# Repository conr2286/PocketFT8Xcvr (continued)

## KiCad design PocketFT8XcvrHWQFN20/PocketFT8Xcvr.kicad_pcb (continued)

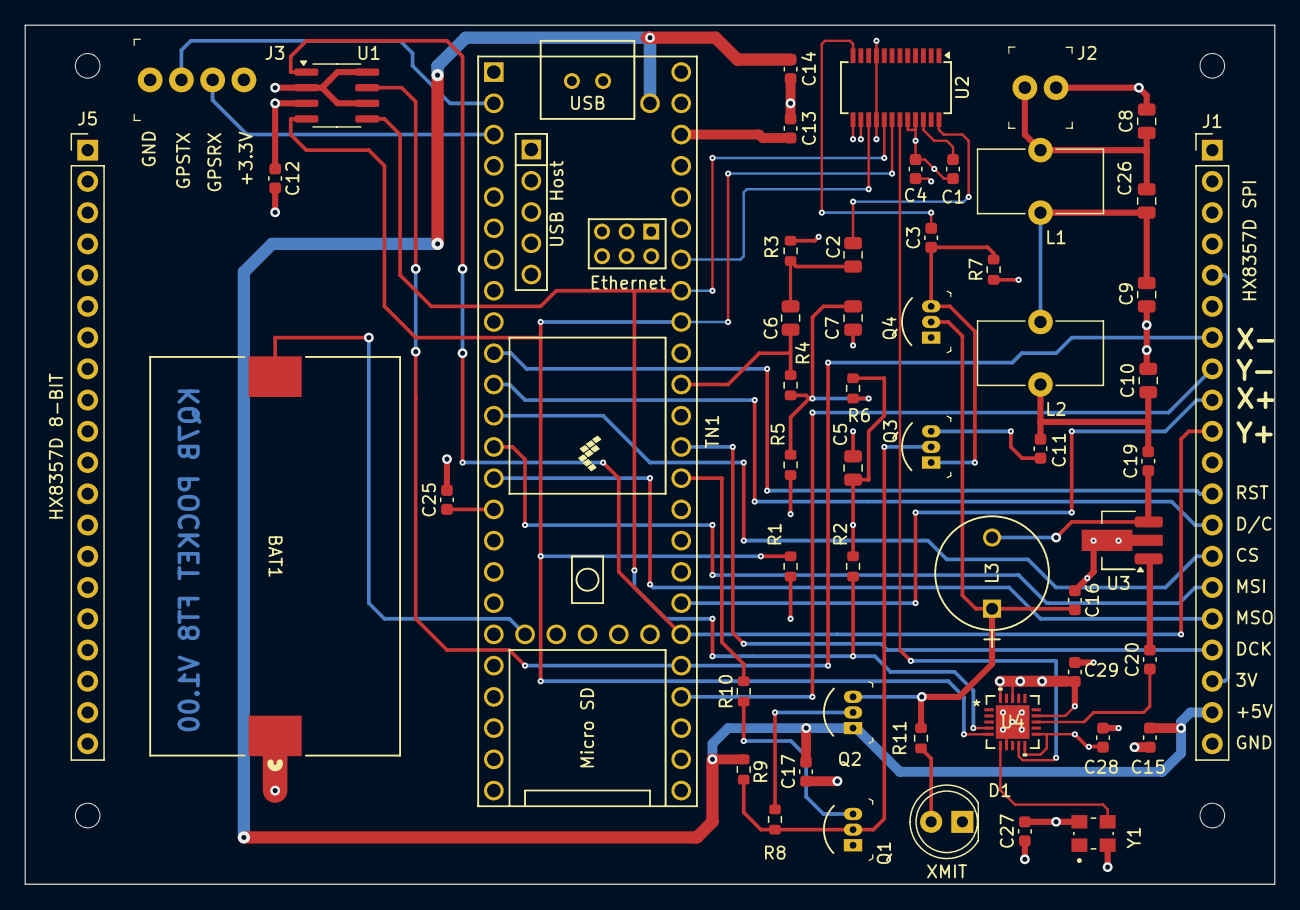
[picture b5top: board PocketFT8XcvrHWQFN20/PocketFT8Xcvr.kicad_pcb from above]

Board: 4 copper layers, 101.6 x 69.9 mm, 54 parts (0 on the bottom side), 42 nets.

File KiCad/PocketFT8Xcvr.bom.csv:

Reference,Value,Footprint,Qty,#,Manufacturer,Description,Notes,Mfg Part #,Type
Y1,ASTX-H11-25.000MHZ-T,ASTX_H11_25_000MHZ_T:XTAL_ASTX-H11-25.000MHZ-T,1,1,Abracon,ASTX-H11-25.000MHZ-T.  -30 ~ +75C,,ASTX-H11-25.000MHZ-T,SMD
U3,GVA-84+,Package_TO_SOT_SMD:SOT-89-3_Handsoldering,1,2,Mini-Circuits,"DC-7000MHz +16dB Gain Block, SOT-89",hand soldering footprint used for better heat sink,GVA-84+,SMD
U2,Si4735-D60-GU,Package_SO:SSOP-24_3.9x8.7mm_P0.635mm,1,3,Skyworks Solutions,RF RX AM/FM 153KHZ-279KHZ 24SSOP,,SI4735-D60-GU,SMD
U1,MCP3422A1T-E/SN,Package_SO:SOIC-8_3.9x4.9mm_P1.27mm,1,4,Microchip Technology,IC ADC 18BIT SIGMA-DELTA 8SOIC,,MCP3422A1T-E/SN,SMD
"R9,R10",5.1K,Resistor_SMD:R_0603_1608Metric,2,5,Yageo,RES 5.1K OHM 5% 1/10W 0603,Substitutions OK,RC0603JR-075K1L,SMD
"R8,R11",510 Ohm,Resistor_SMD:R_0603_1608Metric,2,6,Yageo,RES 510 OHM 5% 1/10W 0603,Substitutions OK,RC0603JR-07510RL,SMD
R7,51 OHM,Resistor_SMD:R_0603_1608Metric,1,7,Yageo,RES 51 OHM 5% 1/2W 1210,Substitutions OK,RC1210JR-0751RL,SMD
R6,10K,Resistor_SMD:R_0603_1608Metric,1,8,Yageo,RES 47.0K OHM 1/8W 0805 SMD,Substitutions OK,RC0603JR-0710KL,SMD
"R3,R4",47K,Resistor_SMD:R_0603_1608Metric,2,9,Yageo,RES 47K OHM 1/10W 5% 0603,Substitutions OK,RC0603JR-0747KL,SMD
"R1,R2,R5",2.0K,Resistor_SMD:R_0603_1608Metric,3,10,Yageo,RES 2K OHM 5% 1/10W 0603,Substitutions OK,RC0603JR-072KL,SMD
IC1,SI5351C-B-GM1,SI5351C-B-GM1:QFN50P300X300X90-17N-D,1,11,Skyworks,"Clock Generators & Support Products I2C programmable, any-frequency, any-output, reference clock input, 4-output LVCMOS clock generator",,,
"C2,C5,C6,C7",10UF,Capacitor_SMD:C_0805_2012Metric,4,12,Kemet,CAP CER 10UF 16V X5R 0805,Substitutions OK,C0805C106K4PAC7800,SMD
"C1,C3,C4,C11,C12,C13,C14,C15,C16,C17,C19,C20,C25,C27,C28,C29",0.1UF,Capacitor_SMD:C_0603_1608Metric,16,13,Kemet,CAP CER 0.1UF 16V X7R 0603,Substitutions OK,C0603C104K4RAC7867,SMD
BAT1,BU2032SM-JJ-GTR,BU2032SM-JJ-GTR_MPD,1,14,MPD (Memory Protection Devices),BATT HOLDER COIN 20MM 1 CELL SMD,Must mount topside,BU2032SM-JJ-GTR,SMD

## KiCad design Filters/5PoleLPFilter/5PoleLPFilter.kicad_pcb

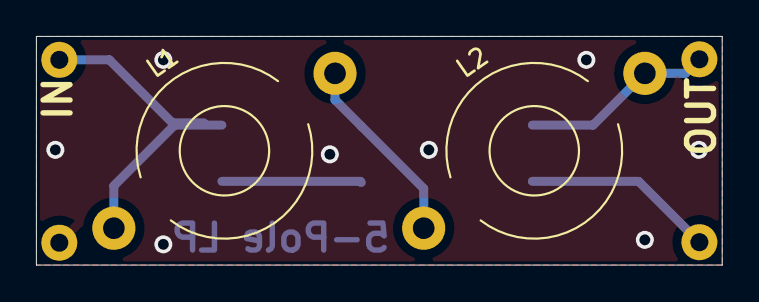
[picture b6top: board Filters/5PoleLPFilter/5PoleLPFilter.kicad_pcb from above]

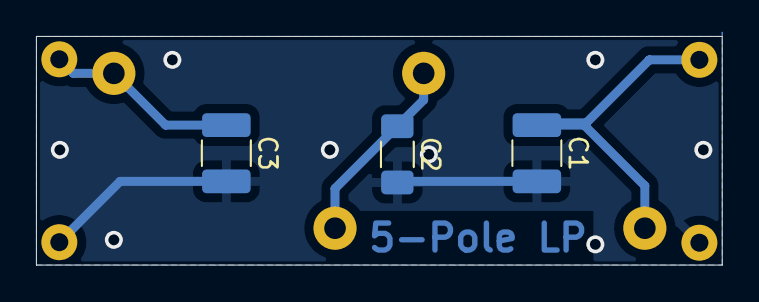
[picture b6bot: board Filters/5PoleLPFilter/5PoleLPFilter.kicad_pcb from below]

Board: 2 copper layers, 38.1 x 12.7 mm, 6 parts (3 on the bottom side), 4 nets.

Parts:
C1, C3: 1000pF; C_1210_3225Metric_Pad1.33x2.70mm_HandSolder
C2: 1300pf; C_1206_3216Metric_Pad1.33x1.80mm_HandSolder
J1: FilterConn02
L1, L2: 1.2uH; L_Toroid_Horizontal_D9.5mm_P15.00mm_Diameter10-5mm_Amidon-T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

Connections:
GND: C1.2, C2.2, C3.2, J1.2
unnamed: C1.1, L1.1
unnamed: C2.1, L1.2, L2.1
unnamed: C3.1, L2.2

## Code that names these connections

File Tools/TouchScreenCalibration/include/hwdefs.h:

#pragma once
/*
**
** NAME
**  pins.h --- Define usage of all GPIO pins in this one place
**
** NOTES
**  If you change processors, displays, etc, you may need to reevaluate the GPIO pin assignments
**
**  Many of the PIN_* names reflect their labels in the schematic
**
**  The V2.0 boards control the RCV and XMT signals using firmware thru PIN_RCV and PIN_XMT.
**  This firmware implementation is compatible with both V1.X and V2.0 boards.
**
**  V2.X and V3.X boards use an MCP342X external 12-bit ADC to read the touchscreen signals.
**
**  V4.X boards eliminate the MCP342X and read the touchscreen through ADC1 A16 and A17 while
**  the Teensy 4.1 audio pipeline uses ADC2 and A2.
**
** HISTORY
**  10/08/2024 Teensy 4.1 pin assignments by KQ7B
**  03/14/2026 Version 4.X boards move the touchscreen to Teensy 4.1's A16 and A17 pins
**
**/

// Define the hardware version number (whole integral values only)
// #define HW_VERSION 2        //Version 2.X boards (working lab prototype)
// #define HW_VERSION 3        // Version 3.X boards (never mfg'd due to tariffs)
#define HW_VERSION 4  // Version 4.X boards (uses internal touchscreen ADC)

// The Adafruit 480x320 display pins
#define PIN_CS 10
#define PIN_DC 9
#define PIN_DRST 8
#define PIN_MOSI 11
#define PIN_DCLK 13  // Teensy 4.1
#define PIN_MISO 12

// I2C pins
#define PIN_SCL 19   // Wire
#define PIN_SDA 18   // Wire
#define PIN_SCL2 24  // Wire2
#define PIN_SDA2 25  // Wire2

// I2C bus definitions for the Wire objects
#define WIRE_RCV Wire   // The SI4735's private bus
#define WIRE_ETC Wire2  // Everything (SI5351, MCP342x) else

// Serial bus definitions for optional GPS
#define SerialGPS Serial1

// SI4735 pins
#define PIN_RRST 20  // Resets the Si4735
#define PIN_AF A2    // Si4735 received audio connected to A2 via Pin 16

// Transmit/Receive pins
#define PIN_XMT 14  // Teensy 4.1
#define PIN_RCV 15  // FW implementation of ~PTT (i.e. RECV) in V2.0 boards

// Adafruit resistive touchscreen pins (External ADC HW option)
#define PIN_YR 38  //
#define PIN_XR 37  //
#define PIN_YM 36  // Any digital pin
#define PIN_XP 39  // Any digital pin

#if HW_VERSION >= 4
// Version 4.X hardware internal Teensy 4.1 ADC pins (Note:  Versions 2.X and 3.x
// use an external ADC read via I2C rather than an internal ADC) for reading the
// touchscreen pins (Schematic signals XDM and YDP).  Note:  You can
// patch a V3.X PCB to make these signal connections for the internal ADC
#define PIN_XM A16  // Y-Coord analog input signal sampled from display's floating XM pin (A16)
#define PIN_YP A17  // X-Coord analog input signal sampled from display's floating YP pin (A17)
#endif

// GPS pins (Teensy 4.1 Serial1)
#define PIN_GPSTX 0  // TX data from GPS
#define PIN_GPSRX 1  // RX data from GPS
#define PIN_PPS 2    // PPS pulse

// Auxilliary pins for future expansion (Require V3+ PCB)
#define PIN_AN13 27  // A13
#define PIN_D27 27   // D27
#define PIN_D28 28   // D28
#define PIN_D29 29   // D29
#define PIN_D30 30   // D30
#define PIN_D31 31   // D31

// The ADC calibration data for V4.X hardware is using a 3.3V reference to Vcc
// And analog.c is using a 10-bit resolution rather than the MCP342X 12-bits.
#if HW_VERSION >= 4
#define TS_MINX (137 >> 2)
#define TS_MINY (126 >> 2)
#define TS_MAXX (2182 >> 2)
#define TS_MAXY (1392 >> 2)
#define MINPRESSURE (120 >> 2)  // I don't think the pressure stuff is working as expected
#define PENRADIUS 3
#else
// This is calibration data for the MC342x ADC to the screen coordinates
// using 510 Ohm resistors to reduce the sensors' driven voltage to Y+ and X-
// where the ADC reference voltage is 2.048 volts, and sampling at 12-bits.
#define TS_MINX 123
#define TS_MINY 104
#define TS_MAXX 1715
#define TS_MAXY 1130
#define MINPRESSURE 120  // I don't think the pressure stuff is working as expected
#define PENRADIUS 3
#endif

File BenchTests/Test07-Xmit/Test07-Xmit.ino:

/**
NAME
  Test07-Si5351 -- Test the entire transmitter's RF chain

DESCRIPTION
  Initializes the Si5351 and programs CLK0 and CLK2.  If successful,
  CLK0 (XCLK, the transmitter clock) will output a 14100 kHz signal.
  Both signals should be confirmed with a frequency counter at the
  antenna connector.

EXERCISED,
  + I2C bus
  + Si5351 connectivity
  + TCXO and Si5351 operation
  + PTT and transmitter's RF chain
  + V2.00 hardware implements the complementary XMIT and RECV signals in firmware
  + V2.00 hardware moved the SI5351 from the Wire to Wire1 bus

NOTE
  + This is the first use of the TCXO whose 25.000 mHz signal
  appears on its pin 3 and on the Si5351 CLKIN pin 6
  + The CLK0 XCLK signal appears on Si5351 pin 13, C20 and U3 pin 1
  + The CLK2 RCLK signal appears on Si5351 pin 9 and Si4735 pin 19

REFERENCES


ATTRIBUTION
  KQ7B 

**/

#include "si5351.h"
#include <Wire.h>

// Set I2C bus to use: Wire, Wire1, etc.
#define WIRE Wire2

//Exercise the Push-to-Talk Pin
#define PIN_PTT 14
#define PIN_RCV 15

Si5351 si5351;

void setup() {
  bool err;

  Serial.begin(9600);
  delay(100);
  printf("Starting...\n");

  //Initialize SI5351 (load cap won't actually be used with CLKIN) for Pocket FT8
  bool found = si5351.init(SI5351_CRYSTAL_LOAD_8PF, 25000000, 0L);
  if (!found) {
    printf("Error:  SI5351 not found\n");
    while (1)
      ;  //Hang here
  }

  //Configure SI5351 PLLs to use external CLKIN rather than XTAL
  si5351.set_pll_input(SI5351_PLLA, SI5351_PLL_INPUT_CLKIN);  //KQ7B V1.00 uses cmos CLKIN, not a XTAL
  si5351.set_pll_input(SI5351_PLLB, SI5351_PLL_INPUT_CLKIN);  //All PLLs using CLKIN
  si5351.set_pll(SI5351_PLL_FIXED, SI5351_PLLA);
  si5351.set_freq(3276800ULL, SI5351_CLK2);  //Receiver's PLL clock (so sad)
  si5351.output_enable(SI5351_CLK2, 1);      //Enable receiver clk (TP3 on PCB)

  //Configure xmit CLK0 for 14.1 mHz
  err = si5351.set_freq(1410000000ULL, SI5351_CLK0);
  if (err) {
    printf("Error:  set_freq(...,CLK0\n");
    while (1)
      ;
  }
  si5351.output_enable(SI5351_CLK0, 1);  //Enable transmitter clk (TP2 on PCB)


  //Turn on the transmitter's RF chain
  pinMode(PIN_RCV, OUTPUT);
  pinMode(PIN_PTT, OUTPUT);
  digitalWrite(PIN_RCV, LOW);   //~RCV
  digitalWrite(PIN_PTT, HIGH);  //XMT
}


void loop() {

  //Output SI5351 status every 10 seconds
  si5351.update_status();
  Serial.print("SYS_INIT: ");
  Serial.print(si5351.dev_status.SYS_INIT);
  Serial.print("  LOL_A: ");
  Serial.print(si5351.dev_status.LOL_A);
  Serial.print("  LOL_B: ");
  Serial.print(si5351.dev_status.LOL_B);
  Serial.print("  LOS: ");
  Serial.print(si5351.dev_status.LOS);
  Serial.print("  REVID: ");
  Serial.println(si5351.dev_status.REVID);

  delay(10000);
}

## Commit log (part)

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2024-10-26 Ongoing filter daughter board development
2024-10-28 Both the main board and filter board submitted to PCBway
2024-11-07 Document xmit/recv switching better
2024-11-07 Better documentation of xmit/recv switching
2024-11-11 40 Meter Bandpass Filter LTspice Simulation
    LTspice was used to evaluate the performance of the 40M bandpass filter
2024-11-22 Preparing bench tests and investigations for V2.00 hardware
    V2.00 hardware has a second I2C bus, a new SN74ACT244 PA, serial support for a GPS, and the complimentary XMT/RCV signals are now implemented in firmware to avoid an unnecessary gate.
2024-11-27 Ongoing prep for V2.00 hardware
2024-11-27 future ideas
2024-12-02 Investigating I2C failure on V2.00 HW
2024-12-03 Resolve Issue #24. Test04-I2C didn't find the SI4735 on SDA/SCL
2024-12-04 Fixing tests for V2.00 boards
2024-12-05 Debugging SI5351 test
    Output frequency off by 100X??? Does set_freq() really want 1/100 Hz resolution? Or has something went wrong?
2024-12-06 Ongoing turn-on of V2.00 boards
2024-12-08 Cleaning up I2C bus definitions
2024-12-08 Tinkering with pins to exercise V1.10 hardware
2024-12-08 tinkering with old recvr code
2024-12-09 Working on gps time
2024-12-09 Issue #23: Isolating SI4735 on a private I2C bus resolves noise/reception issue
    The V2.00 hardware places SI4735 on Wire, and the SI5351 and MCP342x on Wire2 busses.
2024-12-09 Switching to revised version of Test05-Touchpad
2024-12-10 Filter investigations
2024-12-11 Ongoing work to get GPS derived date, time and location working
2024-12-11 Ongoing work on GPS
2024-12-12 Cleaning up some of the dangerous string copies
2024-12-12 Ongoing cleanup of dangerous string operations
2024-12-13 Ongoing prep for logging ADIF
2024-12-13 Ongoing prep work for logging
2024-12-18 Ongoing implementation of logging
2024-12-21 Gathered all the filter designs/models into one folder
2024-12-29 In progress: Instrumenting code to learn about FT8 decoding and howto log a qso
2024-12-29 Ongoing investigation of decoded messages and how CQ is handled
2024-12-31 New bandpass filter PCB and ft8 decoding investigation
2025-01-04 Ongoing investigation of ft8 decoding
2025-01-06 Installing debugging code for transmitted FSK #38
2025-01-11 #39 Transmit timing greatly improved
    Now running a couple hundred milliseconds late.
2025-01-12 Minor GUI improvements
2025-01-21 Mitigate time spent in fillRect() erasing displayed messages
2025-01-22 Misc performance improvements around displaying received messages
    fillRect() is amazingly slow! :(
2025-01-27 Ongoing development of Sequencer
    unpack:202 is recognizing RR73 as a locator
2025-02-02 Sequencer can call CQ and sustain QSO with 2nd KQ7B operator
2025-02-03 Sequencer bug fixes
2025-02-03 Code now builds with Visual Studio Code and PlatformIO
2025-02-03 Testing VSC source control
2025-02-04 Debugging Sequencer in progress
2025-02-04 Moved logging code in .../lib folder
2025-02-07 GPS PPS
2025-02-07 Add PPS signal to hardware
2025-02-07 Info message enhancements
2025-02-07 Sequencer messaging tweeks
2025-02-11 Pocket FT8 Revisited made a QSO with a real remote station
2025-02-12 ADIF logging is now working
2025-02-12 Reorganizing
2025-02-12 Ongoing reorganization of custom library code
2025-02-12 Updating documentation for PlatformIO and V2.00
2025-02-19 Update Sequencer.cpp
    timeslotEvent() was missing a case for LISTEN_RRR
2025-02-19 Fix #54 and #55
    ADIF log now reports transmitter power and rig name.
    Sequencer now distinguishes "CQ" from "CQ DX" and related targeted CQs
2025-02-20 Housekeeping for upcoming release
2025-02-20 Enable RoboOp to automatically respond to CQ messages
2025-02-22 Work on #56 in progress
2025-02-25 Misc cleanup and memory savings
2025-03-02 Ongoing evolution of a host datalink
2025-03-17 Moved CommLink Folder to Investigations
    Pivot to a mechanical solution for extracting ADIF log file
2025-03-18 Cleanup after removing CommLink
2025-03-20 #57 GUI now indicates RECEIVE/PENDING/TRANSMIT/TUNING
2025-03-21 Cleanup
2025-03-23 Now using FT8Font replacing 5X7 font
2025-03-28 A_GUI implementation in progress in Investigations
    + Bug fixes for HX835_t3n which fails to include SP char in getTextBounds() calculation. FIx: Treat ' ' like a '_' char.
2025-03-29 Investigating use of an ADisplay virtual base class
2025-03-30 Cleanup of AGUI before implementing more widgets
2025-04-06 AGUI progress
2025-04-06 AListBox working code cleanup
2025-04-08 AGUI reorganization of app defaults
2025-04-08 Ongoing AGUI
2025-04-09 AGUI AListBox and AButton now pass simple tests
2025-04-10 cleanup stash
2025-04-11 AGUI ongoing develppment
2025-04-11 Rename AGUI investigation folder
2025-04-11 Brought lib AGUI into PocketFT8XcvrFW
2025-04-12 Several AGUI widgets passing user interface tests
2025-04-13 AGUI cleanup
2025-04-15 Ongoing implementation of AGUI in Pocket FT8 Revisited
2025-04-16 Ongoing AGUI test/feature development
2025-04-16 Connect XCLK to MCU
    We may use the GPS PPS timing signal to instrument the accuracy of XCLK operating at, say, 1 mHz and thus derive a calibration adjustment for the TCXO.
2025-04-18 AGUI Tests passing
2025-04-19 Implemented StationInfo in AGUI
2025-04-20 Ongoing AGUI integration
2025-04-20 Ongoing integration of AGUI
2025-04-22 Rewrote AListBox which now passes tests
2025-04-23 Implemented timeout for ancient Station Messages
2025-04-23 Updated LOGFILE.ADIF example
2025-04-23 Move some code to FLASHMEM
2025-04-23 Updated documentation
2025-04-25 Misc UI
2025-04-27 Adding UI support for touching Station Messages
2025-04-27 Enhancements and bugfixes related to new GUI
2025-04-27 Copilot review of AListBox
2025-04-27 Version 2.10
2025-04-29 Refactoring externs
2025-04-30 Refactoring
2025-04-30 Bug fixing
2025-05-01 20M 5-Pole Chebyshev LP Filter
2025-05-02 test_snprintf
2025-05-13 Implement Decode() constructor
2025-05-18 refactor and bug fix
2025-05-20 Reviewing and refactoring
2025-06-06 Update doc
2025-06-06 investigating drawpixel issue in waterfall
2025-07-13 Reordered GPS pins to align with Adafruit Ultimate GPS PA1616S
2025-07-17 Cleanup PCB in progress
2025-07-18 PCB Cleanup
    + GPS signal pins now align with Adafruit's Ultimate GPS to simplify cable
    + Added PPS pin to GPS signals
    + Added extra connector for Teensy analog/digital expansion pins
2025-07-18 PCB V3.00 Cleanup
2025-07-18 Update doc for V3.00 hardware
2025-08-21 V3.00 hardware
2025-09-01 Free Text Messages implemented for buttons M0, M1 and M2 using text from CONFIG.JSON
2025-09-01 Remove DEBUG msgs
2025-09-01 Build on main (new load map)
2025-09-04 Updated doc and exploring Teensy RTC in more detail
2025-09-15 Document MINIMUM_FREQUENCY and MAXIMUM_FREQUENCY
2025-09-15 Create 20Meters.tar.gz
    20Meters.tar.gz contains *eveything* (including hidden .pio files) for a 20 Meter build in .../PocketFT8XcvrFW/.pio/build/teensy41/firmware.hex
2025-09-16 Ignore the load map and comment-out WireIMXRT.h from MCP342x.cpp
2025-09-16 Ignore map
2025-09-17 Ignoring *.map in the future
2025-09-17 Use Charley's PocketFT8XcvrFW with his amplifier stage in audio pipeline
2025-09-17 Place DEFAULT, MINIMUM & MAXIMUM_FREQUENCY in config.h
2025-09-18 Operating frequency now determined entirely by CONFIG.JSON "frequency" entry
2025-09-18 Make hex/firmware.hex available
2025-09-18 Improving RoboOp documentation
2025-09-19 Update commentary in timeslotEvent()
2025-09-19 More documentation of Sequencer.cpp
2025-09-19 Charley's BFO_Offset fix
2025-09-21 Cleanup AGUI documentation (Issue #79)
2025-09-23 Add configurable tcxoCorrection
    Specified in CONFIG.JSON in Hz units
2025-09-24 Removed Changes Made in previous commit.
    Removed Changes Made in previous commit.
    This code agrees with the version on my machine.
2025-10-01 Minor tweaks/doc
2025-10-01 Reorganized tests and added test_touch
2025-10-06 mysteries
2025-10-15 Ready to begin testing callsign hashing
2025-10-16 All unity tests build and pass
2025-10-18 Using new ft8_lib message.cpp, receiver now decodes both standard and nonstandard FT8 message types
2025-10-23 The investigation completed a QSO using a hashed callsign config'd in the Pocket FT8
2025-10-24 Implement unity tests for ft8LibIfce
2025-10-25 Cleaning up crashes arising from new ft8_lib code
2025-10-25 Cleanup DPRINTF, etc
2025-10-25 Refining debug messages
2025-10-25 Ongoing debug refinements
2025-10-26 User real constants in ft8
2025-10-26 Cleanup commentary
2025-11-08 TinySet now passing test_set
2025-12-16 test_agui_covered_widget under development
2025-12-25 AGUI covered widget test in progress
2026-01-21 AGUI now repaints remaining widgets when a widget is deleted
2026-01-22 Ongoing path to separate listening UI from QSO UI
2026-01-25 Debugging new UI
2026-01-25 Moving Station Msg color decisions to UI rather than Sequencer
2026-01-28 Moving UI color and display decisions into UserInterface
2026-01-29 Cleanup following UI changes
2026-01-30 Ongoing refinements/fixes to ui
2026-01-30 Ongoing UI cleanup
2026-01-31 Refactoring UserInterface and Sequencer as Meyers singletons
2026-01-31 Refactor GPShelper as a singleton and eliminate the extern references to its object
2026-01-31 Fixed Sequencer failed to abort CQ
2026-02-02 Refactored AGUI as a Meyers Singleton
2026-02-02 Moved touchscreen calibration parameter into hwdefs.h
2026-02-02 Refactor aspects of waterfall into UserInterface
2026-02-02 Cleanup deprecated code
2026-02-03 Refactor Station as a singleton to clean-up the externs
2026-02-08 Ongoing refactoring and cleanup
2026-02-08 Remove Roger from head of my RSL
2026-02-13 Fixing KiCAD symbols/footprints
    ...damaged by KiCAD upgrade library reorg.
2026-03-08 Minor PCB changes for JLCpcb
2026-03-14 V4 PCB Layout
    Replace MCP342X with Teensy 4.1 internal ADC1 pins A16 and A17
2026-03-14 Minor code cleanups for V4.X
2026-03-14 Submit V4.0 for PCBWay price quote
2026-03-15 Cleanup signal names in firmware to align with schematic
2026-03-15 Disable debugging messages
2026-03-17 V4.01 corrects mistakes in BOM
    Component reduction introduced several errors.
2026-03-19 Cleanup unity tests
2026-03-19 Begin development of hw turn-on test for new boards
2026-03-20 ongoing implementation of test_hw for new boards
2026-03-23 Ongoing hw test development for V4 boards
2026-03-24 Fix missing RCLK signal in test_si4735
2026-03-25 Update 5PoleLP Filter
    + V4.00 Hardware LP Filter PCB
    + Remove deprecated files
2026-03-25 Test cleanup
2026-03-25 Ongoing test development
2026-03-26 touchscreen test investigation
2026-04-14 Ongoing touchscreen improvements
2026-04-14 Ongoing touchscreen work
2026-04-14 Touchpad ongoing
2026-04-16 Copilot bilinear interpolation investigation
2026-04-17 Ongoing touchpad progress
2026-04-18 Ongoing touchscreen calibration
2026-04-23 Touch9 interpolator is working but the AI generated code is... well... in need of improvements.
2026-04-26 TouchScreen calibration investigation continues
2026-04-27 TouchScreenBilinear Interpolator is working at last
2026-04-27 TouchCalibrator code cleanup prior to moving it into a class
2026-04-27 TouchCalibrator now a class
2026-04-29 Serialize/deserialize the TouchCalibrator
2026-05-07 TouchScreen coordinates now follow gfx.setRotation()
2026-05-07 Refactoring and doc
2026-05-08 Ongoing development of TouchScreen calibration
2026-05-11 AGUI now using GFX reference rather than pointer
2026-05-13 Ongoing TestCalibration.cpp development
2026-05-14 Calibrated TouchScreen lib appears more-or-less ready for integration with PocketFT8Xcvr application
2026-05-14 Fix AGUI 's AWidget off-by-one problem in discructor
2026-05-14 Refactor doc
2026-05-15 Removed support for V3.X external MCP342x ADCs. Now requires V4.x or patched V3.X hardware.
2026-05-17 Remove deprecated TouchScreen_I2C code, and repair bug in TouchScreenCalibration
2026-05-20 Implemented hw/test_06 test_TouchPad
2026-05-20 Rotated the screen to place RF SMA and USB power on rear, LED and SD slot on front of enclosure.
2026-05-21 V4.00 hardware is sending/receiving
    LaTex doc underway
2026-05-23 test_UserInterface enhancements
2026-05-25 Ongoing enhancements to test_UserInterface
2026-05-26 Code before Copilot repairs locateCell
2026-05-26 Copilot repair of locateCell()
2026-05-26 Cleanup test_UserInterface
2026-05-26 Further cleanup of test_UserInterface
2026-05-26 Simple changes to debug code
